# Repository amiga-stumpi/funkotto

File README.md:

# FunkOtto

WLAN-Adapter für den Amiga-Parallelport auf Basis des Raspberry Pi Pico 2 W.
Ziel sind eine eigene Firmware, ein SANA-II-Treiber für 68000/AmigaOS 1.3 und
ein Amiga-Konfigurationsprogramm.

## Aktueller Stand

**Aktuelle Hardwarebasis seit 15.10.2026:** Nutzerarchiv `AmiWiFi_Pico2W(1).zip`
mit korrigierten Footprint-Bibliothekskopien und Schaltplan-/Board-Zuordnungen.
[Änderungs- und Prüfbericht](docs/results/2026-10-15-footprint-korrektur.md).
F8-Nachtrag: Alle 58 Symbolpfade korrigiert; native Pfadsuche jetzt 58/58 Treffer.
[Ursache und Nachprüfung](docs/results/2026-10-15-f8-verknuepfung.md).
KiCad 10.0.7: 58 konsistente Footprints, 238 übereinstimmende Pad-Netze,
0 Bibliotheksabweichungen und 0 Schaltplanabgleich-Probleme.
**D2 und R18 stehen noch neben dem Board: Platzierung und drei Verbindungen
sind offen.** ERC: zwei bereits vorhandene Warnungen zu offenen Drahtenden.
Die ursprünglichen 56 Board-Footprints und das bestehende Routing bleiben erhalten.
Aktuelle Berichte: [validation/2026-10-15-footprints/](validation/2026-10-15-footprints/).
Die sonstigen älteren Vorschauen und Prüfberichte sind historische Daten.

[Vorheriger Hardwarestand vom 07.10.2026](docs/results/2026-10-07-revb2.md):
Rev B2 mit U8 SN74LVC2G07DCKR (SC70-6), angepasstem Lötbild und
nativen DRC-/ERC-Prüfberichten. [Bisheriger Fortschritt](docs/results/2026-10-06-fortschritt.md).

Das Repository enthält den [Entwicklungsplan für Firmware v0.1](docs/firmware-v0.1-plan.md)
und das vollständige KiCad-Projekt mit lokalen Bibliotheken, Stückliste und Prüfberichten.
**Die erste Pico-Firmware M1 ist implementiert und als UF2 gebaut:** sichere
GPIO-Zustände, USB-Diagnose (`help`, `info`, `status`) und Watchdog.
[Build- und Testanleitung](firmware/README.md) ·
[Prüfergebnisse M1](docs/results/2026-10-08-firmware-m1.md).
**W1/W2 ist jetzt als WLAN-Testfirmware implementiert:** Scan, RAM-Konfiguration,
WPA2-Verbindung und Wiederverbindung. [Bedienung und Testablauf](firmware/WLAN_TEST.md).
Scan und erster WPA2-Join wurden am 08.10.2026 auf dem Pico bestätigt
(`LINK_UP`, erster Versuch, Join 2679 ms). Manuelles Wiederverbinden und automatische Erholung
nach AP-Ausfall sind ebenfalls bestätigt. Dauerlauf und weitere Fehlerfälle
bleiben offen. **W3 ist implementiert:** Ethernet-Rohtransport mit festen Puffern,
USB-Testprotokoll und PC-Werkzeug für ARP/ICMP. [W3-Testanleitung](firmware/W3_TEST.md) ·
[W3-Prüfstand](docs/results/2026-10-09-w3.md). Die realen ARP/ICMP-Tests sind bestanden:
12/12 und anschließend 1.000/1.000 Echo-Antworten einschließlich MTU 1500,
keine Verluste. Der 1.000er-Lauf ist anhand von JSON und PCAP geprüft.
AP-Ausfall, Wiederverbindung und erneuter Pakettest sind vom Nutzer bestätigt.
Langzeitbetrieb und die Ursache einzelner Latenzausreißer bleiben offen.
**W4 ist implementiert:** dauerhaftes Profil, `wifi save`/`wifi erase` und
Autoconnect nach Stromverlust. [W4-Anleitung](firmware/W4_TEST.md) ·
[W4-Prüfstand](docs/results/2026-10-09-w4.md). Gespeichertes Profil und erster
Kaltstart mit automatischer Wiederverbindung sind am Pico bestätigt. Auch Löschtest
und erneutes Einrichten/Verbinden/Speichern sind bestanden; die weitergehende Hardwareabnahme
bleibt offen.
Parallelport-Kommunikation und Amiga-Treiber folgen.
USB-Diagnose und Kaltstart ohne geöffnetes Terminal wurden am 08.10.2026 vom
Nutzer auf einem realen Pico bestätigt. Die elektrische M0-Abnahme bleibt offen.
**W5 wird auf Nutzerwunsch ausgelassen. M2 ist softwareseitig umgesetzt:**
PIO/DMA-Amiga-Link und 68000-Diagnosetool für HELLO/ECHO.
[M2-Testanleitung](firmware/M2_TEST.md) · [Prüfbericht](docs/results/2026-10-09-m2.md).
Standard-UF2 gesperrt, aktive Bustests nach M0. Der Nutzer hat den portfreien
`FunkOttoDiag SELFTEST` mit 64 ECHOs auf einem Amiga 500 mit 68020,
Kickstart 1.3 und Workbench 1.3 erfolgreich ausgeführt. M2 enthält noch kein WLAN.
[WLAN-Entwicklungsplan](docs/wlan-entwicklungsplan.md).

**M4-USB-Konfiguration:** eigenes Ziel `funkotto_m4_usb` auf W4-Basis,
versionierte Konfigurationsbefehle und PC-Werkzeug `tools/wifi_config.py`.
[Plan](docs/konfigurationsprotokoll-plan.md) · [Testanleitung](firmware/M4_USB_TEST.md) ·
[Protokoll](protocol/CONFIG.md) · [Prüfstand](docs/results/2026-10-10-m4-usb.md).
Trägerplatine noch nicht verfügbar; M0 und aktive M2-Abnahme bleiben offen.

**Amiga-Konfiguration vorbereitet:** `FunkOttoConfig SELFTEST` und `SIM` bieten
einen lokalen FOC1-Selbsttest und eine interaktive Adapter-Simulation mit
verdeckter Passworteingabe. Für 68000 / OS 1.3 gebaut, mit OS-Mocks geprüft;
realer A500-Test und Paralleltransport noch offen. Kein Firmwareupdate nötig.
[Umsetzungsplan](docs/amiga-konfiguration-plan.md) ·
[Amiga-Testanleitung](amiga/config/README.md) ·
[Prüfstand](docs/results/2026-10-10-amiga-config.md).

**Ethernet-Transport am Pico vorbereitet (M5-USB):** FOE1 ist jetzt an den
WLAN-Dienst angebunden: asynchrone TX-Tickets, RX, FOC1, atomare Epochprüfung
und eigener USB-Testmodus. PC-Werkzeug für ARP/ICMP und 1–8 ausstehende Aufträge.
C-/Python-Tests und Pico-Build bestanden; **reale M5-USB-Abnahme offen**.
Parallelport bleibt gesperrt. Nächster Software-Schritt: Amiga-FOE1-Client.
[Plan](docs/ethernet-transport-plan.md) · [Protokoll](protocol/ETHERNET.md) ·
[Testanleitung](firmware/M5_USB_TEST.md) · [Prüfstand](docs/results/2026-10-15-m5-usb.md).

Die erste Firmware soll Parallelport-Kommunikation, WLAN-Rohpakete und ein
dauerhaft gespeichertes WLAN-Profil mit automatischer Wiederverbindung bieten.
Firmwareinstallation und Updates erfolgen vorerst über USB/BOOTSEL am Pico.
Firmwareupdates über den Amiga sind zurückgestellt.

Die Hardwarebasis ist der Nutzerstand vom 15.10.2026 mit Footprint-Korrektur unter [hardware/](hardware/),
auf Grundlage von Rev B2 und der zuvor bearbeiteten Rev-A-Datei. Ein zusätzlicher
Open-Drain-Resetpfad setzt den Pico bei Amiga-Reset oder fehlender Hostversorgung
über RUN zurück. Für v0.1 ist vorgesehen: Nach Reset startet die Firmware neu und verbindet WLAN
erneut; das gespeicherte Profil bleibt erhalten. M1 enthält diese WLAN-Funktion noch nicht.

Für USB/BOOTSEL im Sockel DB25 und USB-C-Trägerversorgung trennen und den
eigenen USB-Anschluss des Pico verwenden; alternativ den Pico herausnehmen.

Die Resetvariante ist in Schaltplan und Board umgesetzt. Pulsbreiten, Pegel,
Versorgungsfolgen und sichere Bustreiberfreigabe müssen vor aktiven Bustests
am Muster gemessen werden (M0 im Plan). Es gibt noch keine Fertigungsfreigabe.

Rev B1 bereinigt die KiCad-Netznamen, Schaltplan-/Footprintattribute,
Bibliothekskopien und Beschriftungen. DRC **mit Schaltplanvergleich** sowie ERC
melden in KiCad 10.0.6 jeweils 0 Fehler und 0 Warnungen. Bauteilpositionen und
Kupferrouting blieben bei B1 unverändert. B2 ändert U8 auf DCKR/SC70-6 und
passte ausschließlich sein lokales Routing an; die damaligen DRC- und ERC-Läufe waren fehlerfrei. Die frühere Rev-B-Prüfung war hinsichtlich
des nativen Schaltplanabgleichs unvollständig; Details und damalige Hardware-
Prüfsummen stehen im Firmwareplan. Aktuelle Prüfsummen stehen im oben verlinkten Importnachweis.

## Ideen und spätere Erweiterungen

Die [Ideenliste](docs/ideenliste.md) sammelt fortlaufend Erweiterungswünsche.
Erster Eintrag: eine später nachrüstbare Traffic-LED, optional getrennt für TX/RX.

## KiCad-Projekt öffnen

Repository herunterladen und `hardware/AmiWiFi.kicad_pro` mit KiCad 10 öffnen.
Die Bibliotheken in `hardware/` gehören zum Projekt.

- [Hinweise zum Hardwarestand Rev B2](docs/KICAD_REV_B2.txt)
- [Stückliste](docs/BOM.csv) und [Pinbelegung](docs/PINOUT.csv)
- [Vorschauen](preview/) und [Prüfberichte](validation/)

Am 15.10.2026 aus dem aktuellen Nutzerarchiv übernommen und die Footprint-Zuordnungen korrigiert.
D2/R18 müssen noch platziert und geroutet werden. Elektrische Musterprüfung
und Fertigungsfreigabe bleiben offen.

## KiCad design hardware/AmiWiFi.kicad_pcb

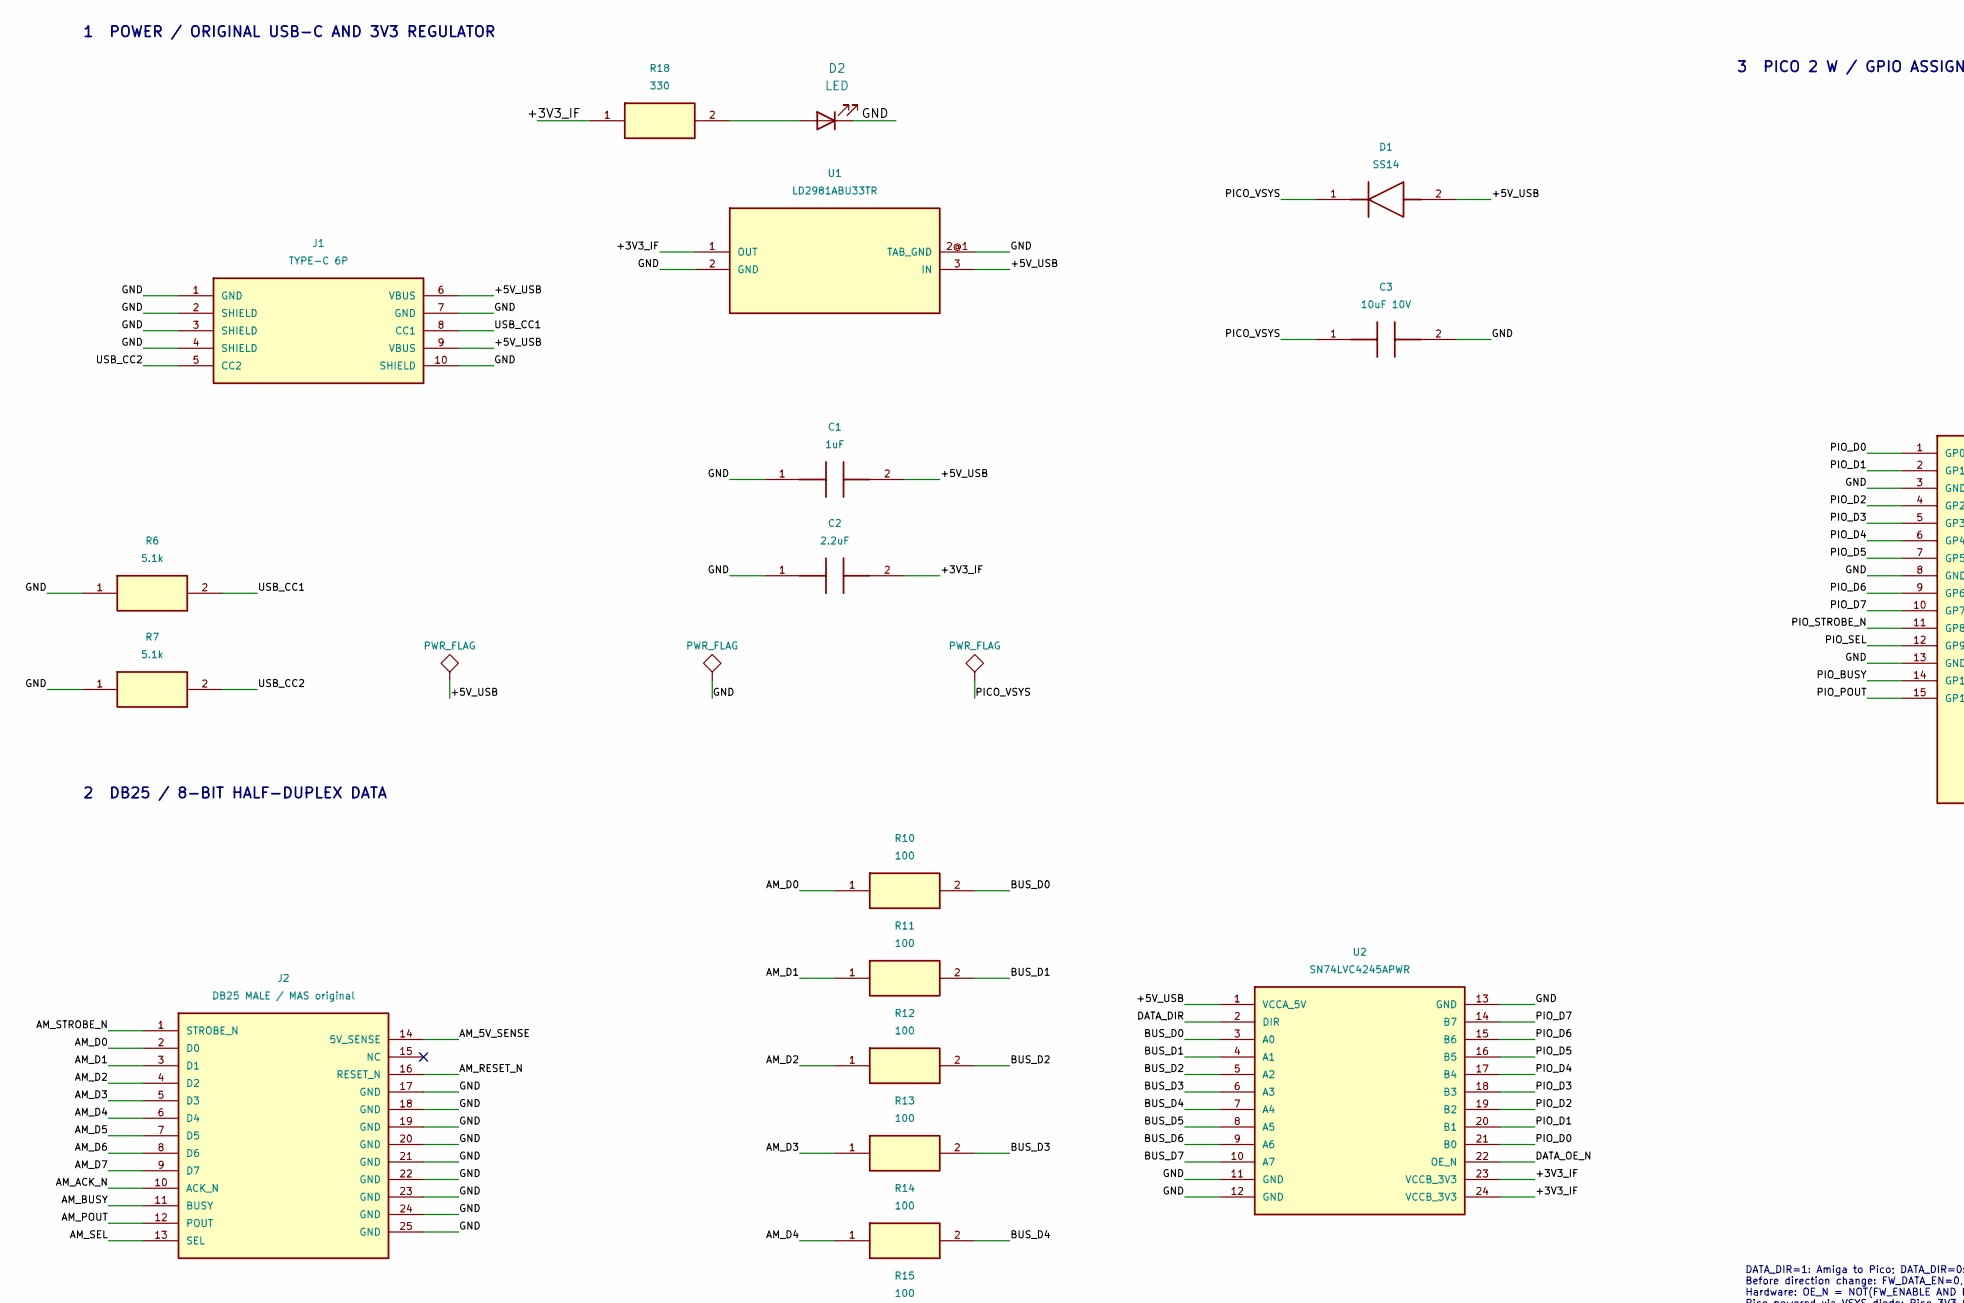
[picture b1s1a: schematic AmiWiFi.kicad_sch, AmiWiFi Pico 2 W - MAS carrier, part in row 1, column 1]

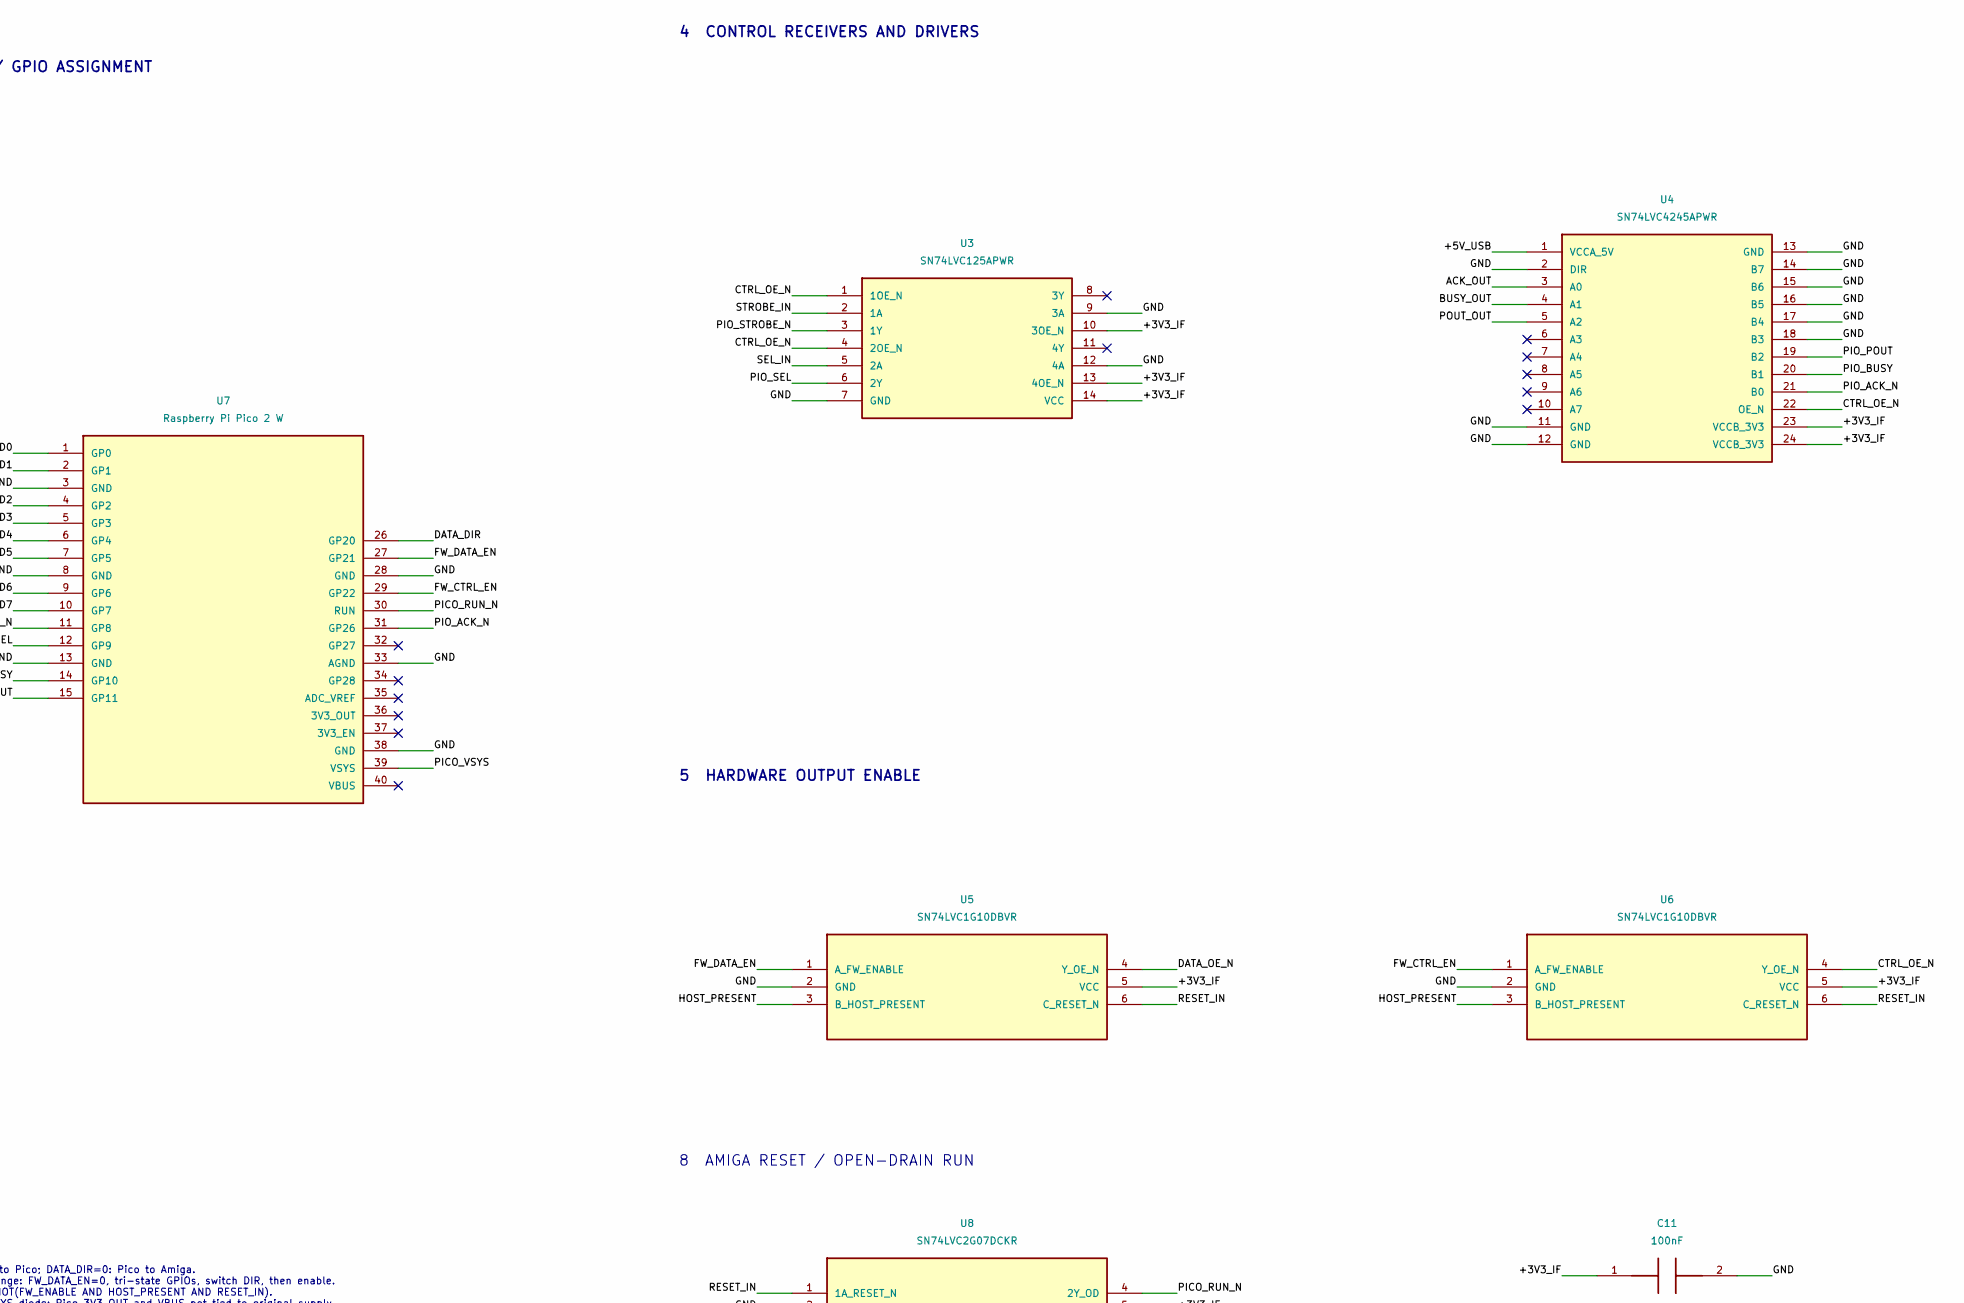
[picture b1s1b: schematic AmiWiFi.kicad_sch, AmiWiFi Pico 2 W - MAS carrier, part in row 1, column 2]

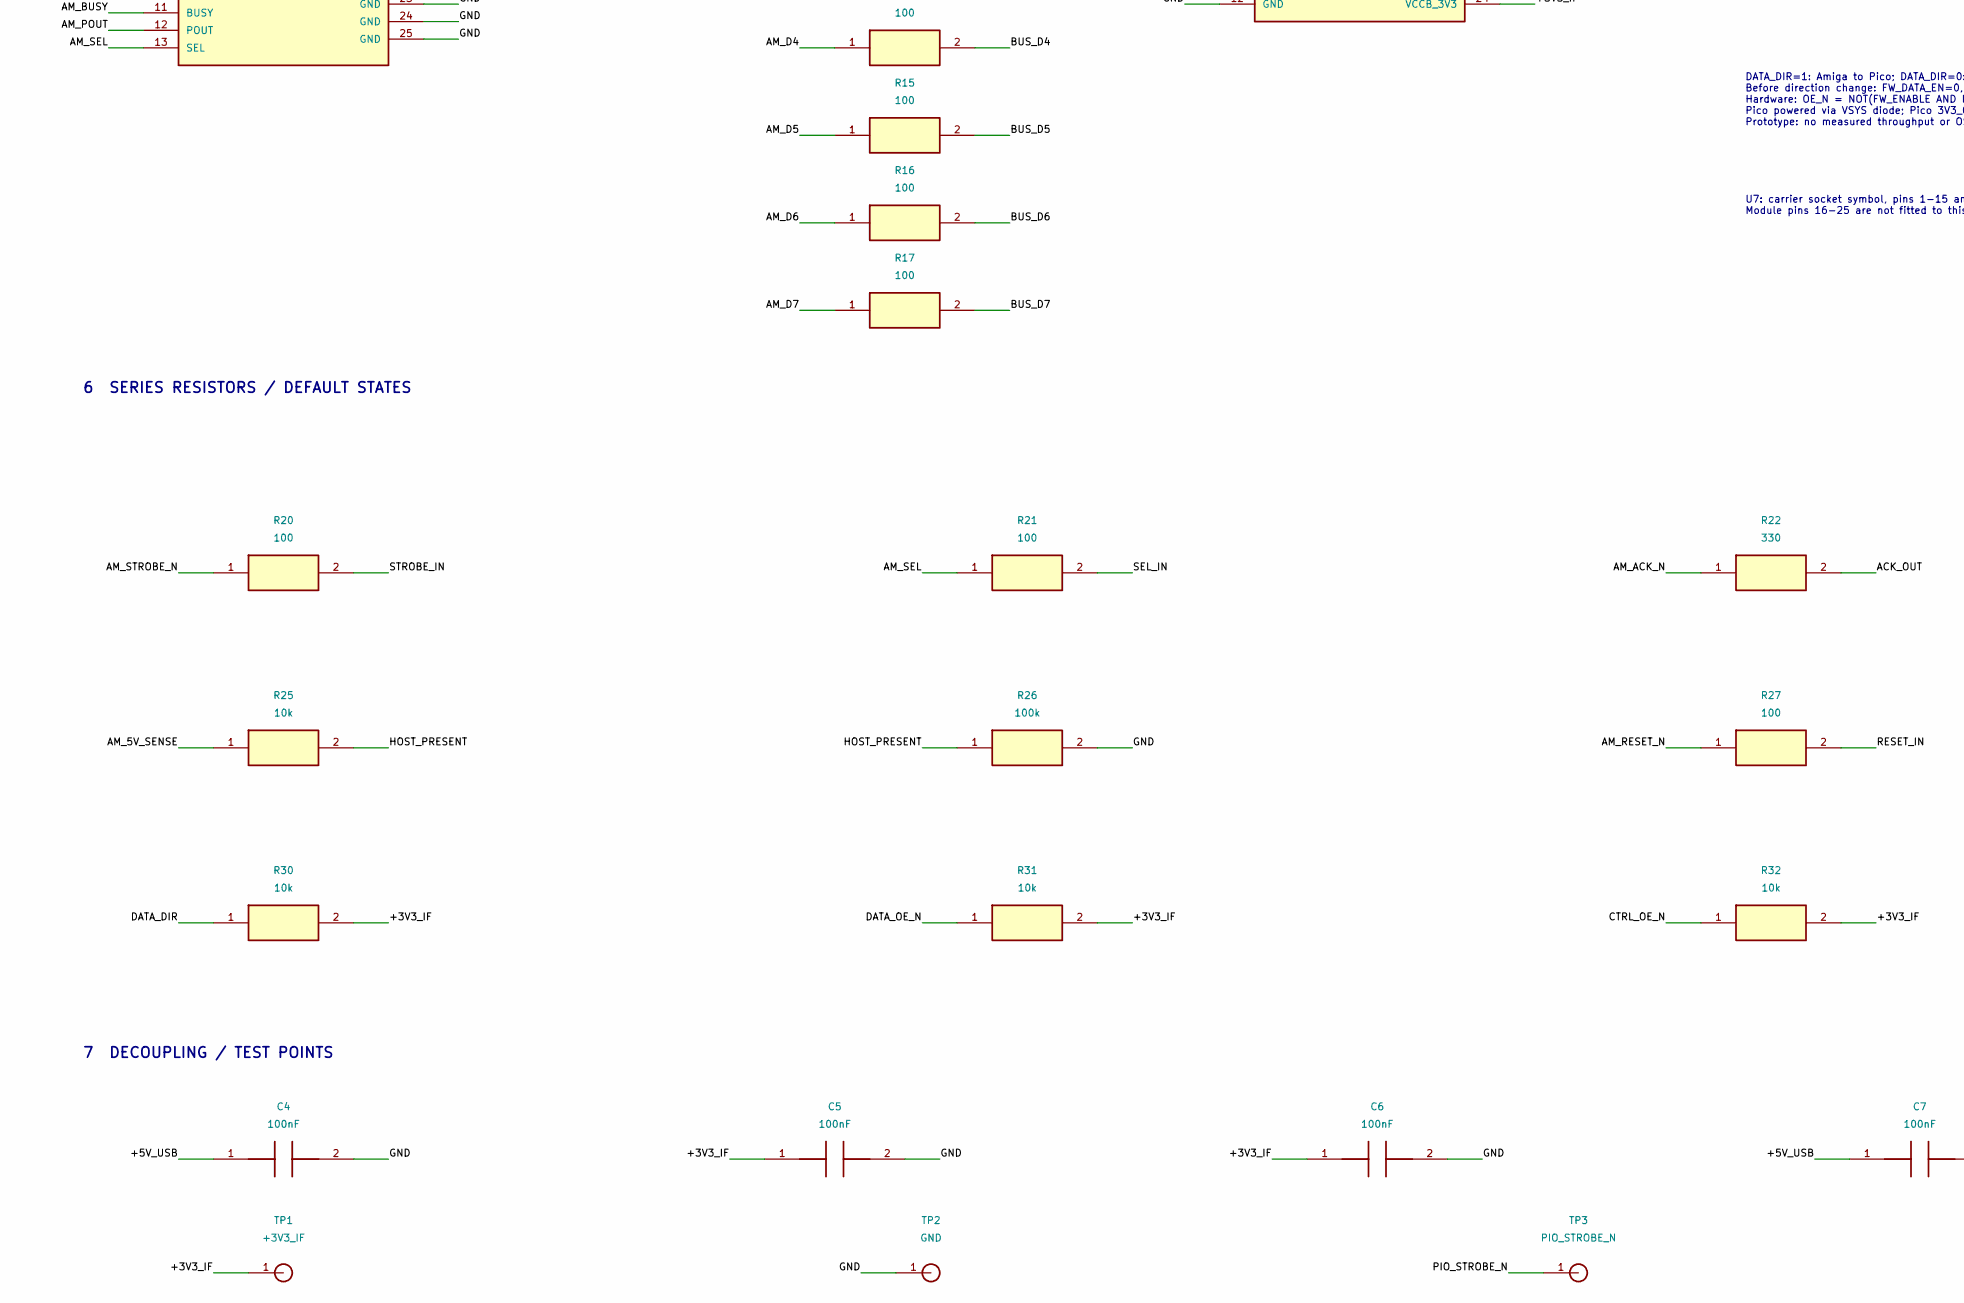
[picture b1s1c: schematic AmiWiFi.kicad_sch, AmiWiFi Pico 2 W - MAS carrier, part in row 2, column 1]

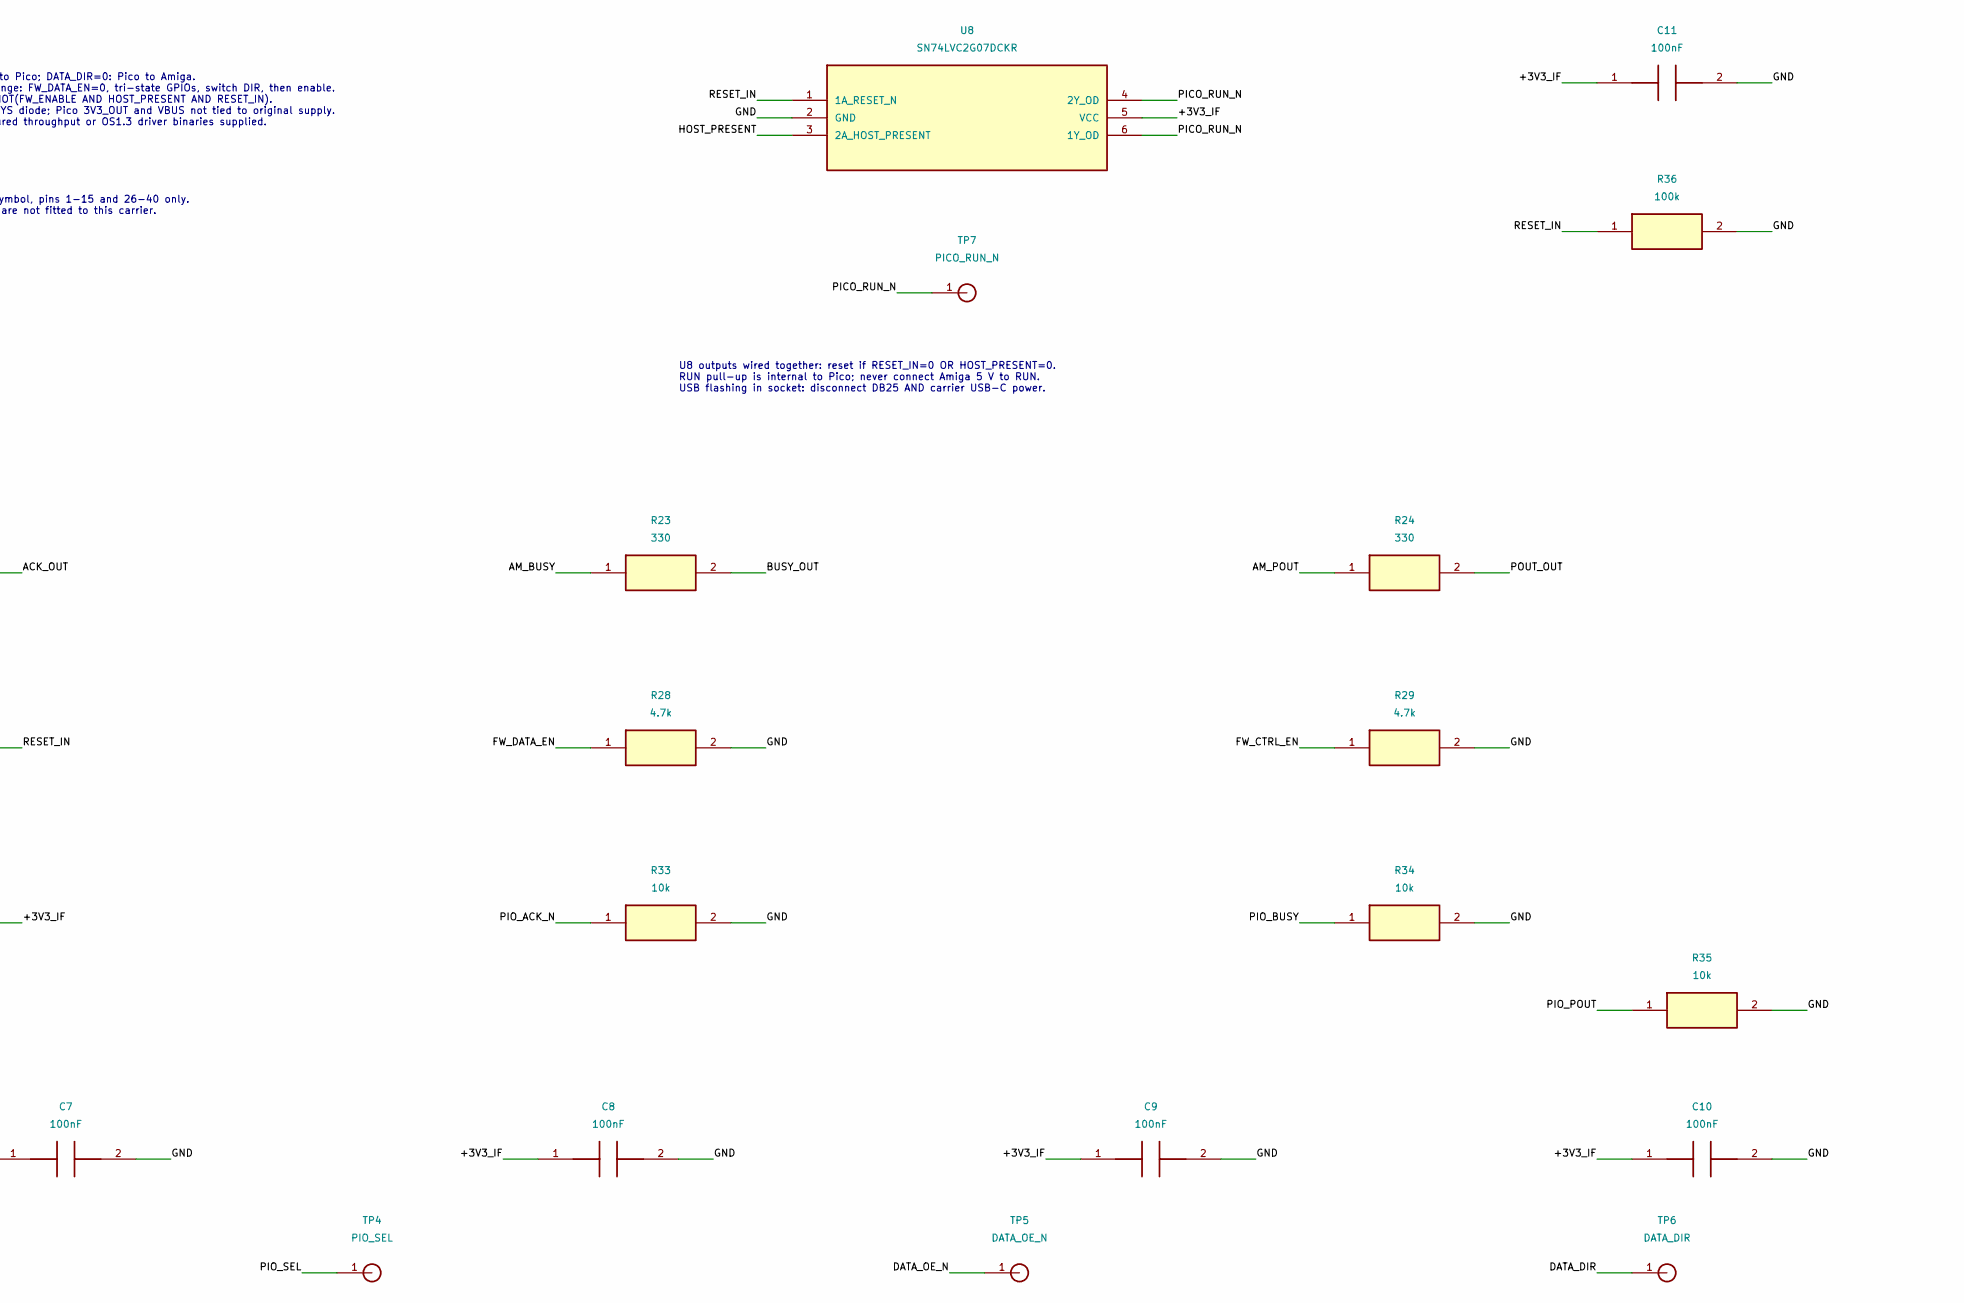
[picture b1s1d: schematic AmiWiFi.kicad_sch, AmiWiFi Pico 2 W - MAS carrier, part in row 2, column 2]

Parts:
C1: 1uF; C0603_MAS_C1
C2: 2.2uF; C0603_MAS_C2
C3: 10uF 10V; C0805_C3
C4: 100nF; C0603_C4
C5: 100nF; C0603_C5
C6: 100nF; C0603_C6
C7: 100nF; C0603_C7
C8: 100nF; C0603_C8
C9: 100nF; C0603_C9
C10: 100nF; C0603_C10
C11: 100nF; C0603_C11
D1: SS14; SOD123_D1
D2: LED; LED_0603_HandSolder_D2; LCSC C2909774
J1: TYPE-C 6P; USB_C_MAS_Original_J1; LCSC C456012
J2: DB25 MALE / MAS original; DB25_MAS_Original_J2
R6: 5.1k; R0603_MAS_R6
R7: 5.1k; R0603_MAS_R7
R10: 100; R0402_R10
R11: 100; R0402_R11
R12: 100; R0402_R12
R13: 100; R0402_R13
R14: 100; R0402_R14
R15: 100; R0402_R15
R16: 100; R0402_R16
R17: 100; R0402_R17
R18: 330; R0402_R18
R20: 100; R0402_R20
R21: 100; R0402_R21
R22: 330; R0402_R22
R23: 330; R0402_R23
R24: 330; R0402_R24
R25: 10k; R0402_R25
R26: 100k; R0402_R26
R27: 100; R0402_R27
R28: 4.7k; R0402_R28
R29: 4.7k; R0402_R29
R30: 10k; R0402_R30
R31: 10k; R0402_R31
R32: 10k; R0402_R32
R33: 10k; R0402_R33
R34: 10k; R0402_R34
R35: 10k; R0402_R35
R36: 100k; R0402_R36
TP1: +3V3_IF; TP1_TP1
TP2: GND; TP1_TP2
TP3: PIO_STROBE_N; TP1_TP3
TP4: PIO_SEL; TP1_TP4
TP5: DATA_OE_N; TP1_TP5
TP6: DATA_DIR; TP1_TP6
TP7: PICO_RUN_N; TP1_TP7
U1: LD2981ABU33TR; SOT89_MAS_Original_U1
U2: SN74LVC4245APWR; TSSOP24_U2
U3: SN74LVC125APWR; TSSOP14_U3
U4: SN74LVC4245APWR; TSSOP24_U4
U5: SN74LVC1G10DBVR; SOT23_6_U5
U6: SN74LVC1G10DBVR; SOT23_6_U6
U7: Raspberry Pi Pico 2 W; Pico2W_PartialSocket_15x2_U7
U8: SN74LVC2G07DCKR; SC70_6_DCK_U8

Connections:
/+3V3_IF: C2.2, C5.1, C6.1, C8.1, C9.1, C10.1, C11.1, R18.1, R30.2, R31.2, R32.2, TP1.1, U1.1 (OUT), U2.23 (VCCB_3V3), U2.24 (VCCB_3V3), U3.10 (3OE_N), U3.13 (4OE_N), U3.14 (VCC), U4.23 (VCCB_3V3), U4.24 (VCCB_3V3), U5.5 (VCC), U6.5 (VCC), U8.5 (VCC)
/+5V_USB: C1.2, C4.1, C7.1, D1.2, J1.6 (VBUS), J1.9 (VBUS), U1.3 (IN), U2.1 (VCCA_5V), U4.1 (VCCA_5V)
/ACK_OUT: R22.2, U4.3 (A0)
/AM_5V_SENSE: J2.14 (5V_SENSE), R25.1
/AM_ACK_N: J2.10 (ACK_N), R22.1
/AM_BUSY: J2.11 (BUSY), R23.1
/AM_D0: J2.2 (D0), R10.1
/AM_D1: J2.3 (D1), R11.1
/AM_D2: J2.4 (D2), R12.1
/AM_D3: J2.5 (D3), R13.1
/AM_D4: J2.6 (D4), R14.1
/AM_D5: J2.7 (D5), R15.1
/AM_D6: J2.8 (D6), R16.1
/AM_D7: J2.9 (D7), R17.1
/AM_POUT: J2.12 (POUT), R24.1
/AM_RESET_N: J2.16 (RESET_N), R27.1
/AM_SEL: J2.13 (SEL), R21.1
/AM_STROBE_N: J2.1 (STROBE_N), R20.1
/BUSY_OUT: R23.2, U4.4 (A1)
/BUS_D0: R10.2, U2.3 (A0)
/BUS_D1: R11.2, U2.4 (A1)
/BUS_D2: R12.2, U2.5 (A2)
/BUS_D3: R13.2, U2.6 (A3)
/BUS_D4: R14.2, U2.7 (A4)
/BUS_D5: R15.2, U2.8 (A5)
/BUS_D6: R16.2, U2.9 (A6)
/BUS_D7: R17.2, U2.10 (A7)
/CTRL_OE_N: R32.1, U3.1 (1OE_N), U3.4 (2OE_N), U4.22 (OE_N), U6.4 (Y_OE_N)
/DATA_DIR: R30.1, TP6.1, U2.2 (DIR), U7.26 (GP20)
/DATA_OE_N: R31.1, TP5.1, U2.22 (OE_N), U5.4 (Y_OE_N)
/FW_CTRL_EN: R29.1, U6.1 (A_FW_ENABLE), U7.29 (GP22)
/FW_DATA_EN: R28.1, U5.1 (A_FW_ENABLE), U7.27 (GP21)
/GND: C1.1, C2.1, C3.2, C4.2, C5.2, C6.2, C7.2, C8.2, C9.2, C10.2, C11.2, D2.1 (K), J1.1 (GND), J1.2 (SHIELD), J1.3 (SHIELD), J1.4 (SHIELD), J1.7 (GND), J1.10 (SHIELD), J2.17 (GND), J2.18 (GND), J2.19 (GND), J2.20 (GND), J2.21 (GND), J2.22 (GND), J2.23 (GND), J2.24 (GND), J2.25 (GND), R6.1, R7.1, R26.2, R28.2, R29.2, R33.2, R34.2, R35.2, R36.2, TP2.1, U1.2 (GND), U1.2@1 (TAB_GND), U2.11 (GND), U2.12 (GND), U2.13 (GND), U3.7 (GND), U3.9 (3A), U3.12 (4A), U4.2 (DIR), U4.11 (GND), U4.12 (GND), U4.13 (GND), U4.14 (B7), U4.15 (B6), U4.16 (B5), U4.17 (B4), U4.18 (B3), U5.2 (GND), U6.2 (GND), U7.3 (GND), U7.8 (GND), U7.13 (GND), U7.28 (GND), U7.33 (AGND), U7.38 (GND), U8.2 (GND)
/HOST_PRESENT: R25.2, R26.1, U5.3 (B_HOST_PRESENT), U6.3 (B_HOST_PRESENT), U8.3 (2A_HOST_PRESENT)
/PICO_RUN_N: TP7.1, U7.30 (RUN), U8.4 (2Y_OD), U8.6 (1Y_OD)
/PICO_VSYS: C3.1, D1.1, U7.39 (VSYS)
/PIO_ACK_N: R33.1, U4.21 (B0), U7.31 (GP26)
/PIO_BUSY: R34.1, U4.20 (B1), U7.14 (GP10)
/PIO_D0: U2.21 (B0), U7.1 (GP0)
/PIO_D1: U2.20 (B1), U7.2 (GP1)
/PIO_D2: U2.19 (B2), U7.4 (GP2)
/PIO_D3: U2.18 (B3), U7.5 (GP3)
/PIO_D4: U2.17 (B4), U7.6 (GP4)
/PIO_D5: U2.16 (B5), U7.7 (GP5)
/PIO_D6: U2.15 (B6), U7.9 (GP6)
/PIO_D7: U2.14 (B7), U7.10 (GP7)
/PIO_POUT: R35.1, U4.19 (B2), U7.15 (GP11)
/PIO_SEL: TP4.1, U3.6 (2Y), U7.12 (GP9)
/PIO_STROBE_N: TP3.1, U3.3 (1Y), U7.11 (GP8)
/POUT_OUT: R24.2, U4.5 (A2)
/RESET_IN: R27.2, R36.1, U5.6 (C_RESET_N), U6.6 (C_RESET_N), U8.1 (1A_RESET_N)
/SEL_IN: R21.2, U3.5 (2A)
/STROBE_IN: R20.2, U3.2 (1A)
/USB_CC1: J1.8 (CC1), R6.2
/USB_CC2: J1.5 (CC2), R7.2
unnamed: D2.2 (A), R18.2

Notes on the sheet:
2 DB25 / 8-BIT HALF-DUPLEX DATA
6 SERIES RESISTORS / DEFAULT STATES
4 CONTROL RECEIVERS AND DRIVERS
U7: carrier socket symbol, pins 1-15 and 26-40 only. Module pins 16-25 are not fitted to this carrier.
1 POWER / ORIGINAL USB-C AND 3V3 REGULATOR
8 AMIGA RESET / OPEN-DRAIN RUN
5 HARDWARE OUTPUT ENABLE
3 PICO 2 W / GPIO ASSIGNMENT
7 DECOUPLING / TEST POINTS
DATA_DIR=1: Amiga to Pico; DATA_DIR=0: Pico to Amiga. Before direction change: FW_DATA_EN=0, tri-state GPIOs, switch DIR, then enable. Hardware: OE_N = NOT(FW_ENABLE AND HOST_PRESENT AND RESET_IN). Pico powered via VSYS diode; Pico 3V3_OUT and VBUS not tied to original supply. Prototype: no measure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
U8 outputs wired together: reset if RESET_IN=0 OR HOST_PRESENT=0. RUN pull-up is internal to Pico; never connect Amiga 5 V to RUN. USB flashing in socket: disconnect DB25 AND carrier USB-C power.

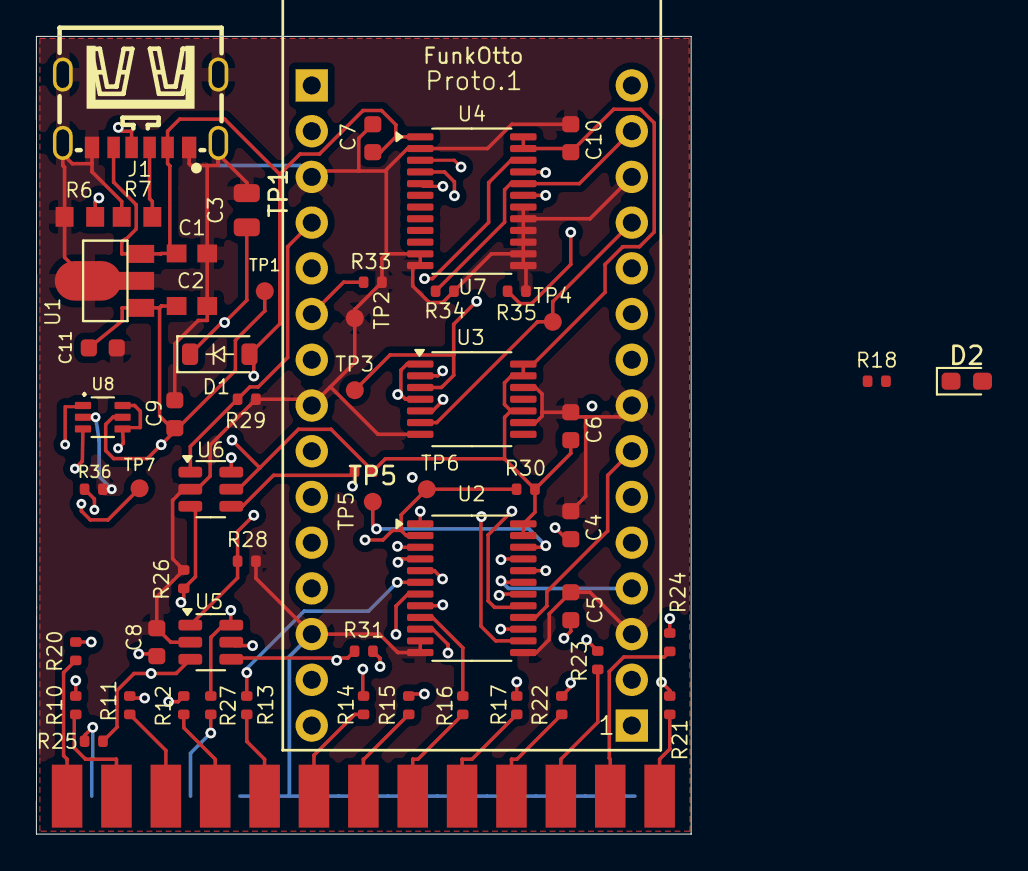
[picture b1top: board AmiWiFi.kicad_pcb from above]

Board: 4 copper layers, 36.4 x 44.3 mm, 58 parts (0 on the bottom side), 56 nets.

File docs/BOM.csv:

Reference,Value / MPN,Footprint,Notes
C1,1uF,C0603_MAS_C1,
C2,2.2uF,C0603_MAS_C2,
C3,10uF 10V,C0805_C3,
C4,100nF,C0603_C4,
C5,100nF,C0603_C5,
C6,100nF,C0603_C6,
C7,100nF,C0603_C7,
C8,100nF,C0603_C8,
C9,100nF,C0603_C9,
C10,100nF,C0603_C10,
C11,100nF,C0603_C11,
D1,SS14,SOD123_D1,External USB to VSYS diode; Pico VBUS is not connected to carrier USB.
D2,LED,LED_0603_HandSolder_D2,"LCSC C2909774; noch neben dem Board, Platzierung/Routing offen"
J1,TYPE-C 6P,USB_C_MAS_Original_J1,
J2,DB25 MALE / MAS original,DB25_MAS_Original_J2,
R6,5.1k,R0603_MAS_R6,
R7,5.1k,R0603_MAS_R7,
R10,100,R0402_R10,
R11,100,R0402_R11,
R12,100,R0402_R12,
R13,100,R0402_R13,
R14,100,R0402_R14,
R15,100,R0402_R15,
R16,100,R0402_R16,
R17,100,R0402_R17,
R18,330,R0402_R18,Vorwiderstand D2; Platzierung/Routing offen
R20,100,R0402_R20,
R21,100,R0402_R21,
R22,330,R0402_R22,
R23,330,R0402_R23,
R24,330,R0402_R24,
R25,10k,R0402_R25,
R26,100k,R0402_R26,
R27,100,R0402_R27,
R28,4.7k,R0402_R28,
R29,4.7k,R0402_R29,
R30,10k,R0402_R30,
R31,10k,R0402_R31,
R32,10k,R0402_R32,
R33,10k,R0402_R33,
R34,10k,R0402_R34,
R35,10k,R0402_R35,
R36,100k,R0402_R36,
TP1,+3V3_IF,TP1_TP1,
TP2,GND,TP1_TP2,
TP3,PIO_STROBE_N,TP1_TP3,
TP4,PIO_SEL,TP1_TP4,
TP5,DATA_OE_N,TP1_TP5,
TP6,DATA_DIR,TP1_TP6,
TP7,PICO_RUN_N,TP1_TP7,
U1,LD2981ABU33TR,SOT89_MAS_Original_U1,
U2,SN74LVC4245APWR,TSSOP24_U2,
U3,SN74LVC125APWR,TSSOP14_U3,
U4,SN74LVC4245APWR,TSSOP24_U4,
U5,SN74LVC1G10DBVR,SOT23_6_U5,
U6,SN74LVC1G10DBVR,SOT23_6_U6,
U7,Raspberry Pi Pico 2 W,Pico2W_PartialSocket_15x2_U7,Rotated 180deg; two 1x15 sockets on module pins 1..15 and 26..40. Antenna overhang 11.3471 mm. Minimum 8.5mm socket spacing recommended. Pins16..25 not soldered.
U8,SN74LVC2G07DCKR,SC70_6_DCK_U8,
